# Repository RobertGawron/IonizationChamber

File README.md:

# Ionization Chamber (a device for measuring radioactivity levels)

## Objective

There are many ionization chamber projects online, but most (though not all) produce false positive results. It's cool when a radioactive sample is placed near the detector and the detector shows an increased radiation value, but then, if you place your hand or any non-radioactive object nearby, the readings are high too. This is because, due to high amplification, these devices pick up a lot of noise, making the measurements unreliable.

This project aims to address and eliminate this issue.

## Principle of operation

An ionization chamber is a type of radiation detector that measures ionizing radiation by detecting the charged particles (ions) produced when radiation interacts with the gas inside the chamber. The basic working principle relies on the ionization process. 

* **Radiation Interaction:** When ionizing radiation (such as alpha, beta, or gamma radiation) enters the chamber, it interacts with the gas inside, typically air. This interaction causes the gas molecules to become ionized, producing free electrons and positive ions. 
* **Electric Field:** The chamber contains two electrodes: a central anode and a surrounding cathode. A high voltage is applied between these electrodes, creating an electric field inside the chamber. 
* **Ion Collection:** The free electrons, which are negatively charged, are attracted to the positive anode, while the positively charged ions are attracted to the cathode. As these ions move toward the electrodes, they create an electrical current. 
* **Current Measurement:** The generated current is directly proportional to the number of ions produced, which in turn is related to the amount of radiation that has passed through the chamber. This current is then measured and used to calculate the intensity of the radiation.

Below is an image of the device that was assembled and tested (hardware revision 4.0). Since then, a new version has been developed but has not yet been tested. This repository, in its current state, represents the latest version. For details on the tested version, [refer to 4.0 tag](https://github.com/RobertGawron/IonizationChamber/releases/tag/4.0).  

## System architecture

It is designed in a way that the device can work remotely, e.g. no connection via USB cable to user’s PC is needed.

Remarks:
* The amplifier has three stages (the first stage is a transimpedance amplifier, not a FET transistor like most projects use).
* The ionization chamber is polarized with three 12V batteries connected in series.

## Hardware

PCB was done in KiCAD.

### Hazards

* **The battery container electrodes for chamber polarization are very close to the metal casing; the soldered electrodes should be filed down and secured with insulating tape to prevent short circuits.**
* **The device uses relatively high voltage (32V) to polarize the ionization chamber.** The electrodes of the ionization chamber should not be touched.

## Software

Measurements are collected from the COM port (tunneled over USB) by a Python script and stored in a .csv file. This file can later be parsed using R scripts to generate various diagrams, such as radioactivity changes over time, radioactivity histograms, and box plots for different samples.

* [Details about the firmware are available here.](./Software/Firmware/README.md)
* [Details about the acquisition software are available here.](./Software/MeasurementAcquisition/README.md)
* [Details about the measurement processing software are available here.](./Software/MeasurementAnalysis/README.md)

In the future, data from the device will be gathered and processed using the [HardwareDataLogger project](https://github.com/RobertGawron/HardwareDataLogger), which is currently in development.

## Simulation

A simple mockup was created to generate dummy test data without the need for the real device. This allows testing of the acquisition software (mainly the scripts that generate output diagrams) without requiring hardware.

[More details.](Simulation/README.md)

## DevOps

All software is developed inside a Docker container.

[More information about setting up the environment.](./Documentation/Manuals/README.md)

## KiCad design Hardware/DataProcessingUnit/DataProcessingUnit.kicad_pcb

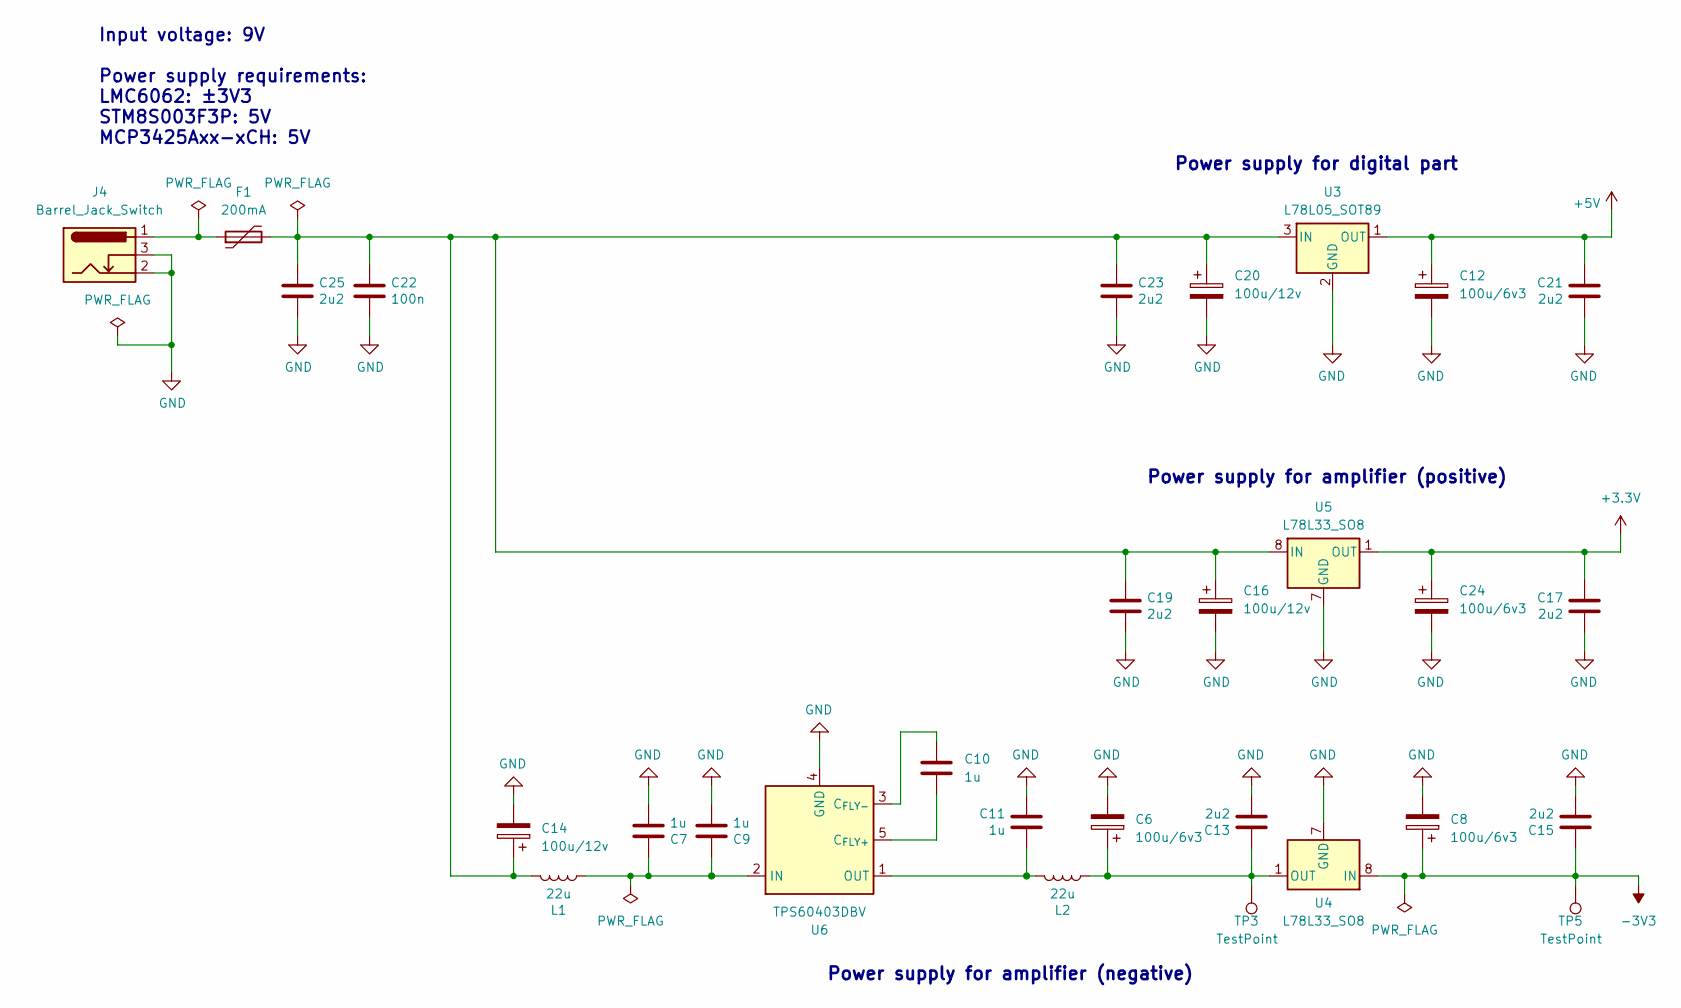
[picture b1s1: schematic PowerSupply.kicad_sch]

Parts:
C6, C8, C24: 100u/6v3; CP_EIA-3528-21_Kemet-B
C7, C9, C10, C11: 1u; C_0805_2012Metric
C12: 100u/6v3; CP_Elec_6.3x5.8
C13, C15, C17, C19, C21, C23, C25: 2u2; C_0805_2012Metric
C14, C16, C20: 100u/12v; CP_Elec_6.3x5.8
C22: 100n; C_0805_2012Metric
F1: 200mA; Fuse_1206_3216Metric
J4: Barrel_Jack_Switch; BarrelJack_GCT_DCJ200-10-A_Horizontal
L1, L2: 22u; L_7.3x7.3_H3.5
TP3, TP5: TestPoint; TestPoint_Pad_D1.0mm
U3: L78L05_SOT89; SOT-89-3
U4, U5: L78L33_SO8; SOIC-8_3.9x4.9mm_P1.27mm
U6: TPS60403DBV; SOT-23-5

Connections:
+3.3V: C17.1, C24.1, U5.1 (OUT); also elsewhere on the board
+5V: C12.1, C21.1, U3.1 (OUT); also elsewhere on the board
-3V3: C8.1, C15.1, TP5.1, U4.8 (IN); also elsewhere on the board
GND: C6.2, C7.2, C8.2, C9.2, C11.2, C12.2, C13.2, C14.2, C15.2, C16.2, C17.2, C19.2, C20.2, C21.2, C22.2, C23.2, C24.2, C25.2, J4.2, J4.3, U3.2 (GND), U4.2 (GND), U4.3 (GND), U4.6 (GND), U4.7 (GND), U5.2 (GND), U5.3 (GND), U5.6 (GND), U5.7 (GND), U6.4 (GND); also elsewhere on the board
unnamed: F1.1, J4.1
unnamed: C14.1, C16.1, C19.1, C20.1, C22.1, C23.1, C25.1, F1.2, L1.2, U3.3 (IN), U5.8 (IN)
unnamed: C6.1, C13.1, L2.1, TP3.1, U4.1 (OUT)
unnamed: C10.2, U6.5 (C_{FLY+})
unnamed: C10.1, U6.3 (C_{FLY-})
unnamed: C7.1, C9.1, L1.1, U6.2 (IN)
unnamed: C11.1, L2.2, U6.1 (OUT)

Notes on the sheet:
Power supply for amplifier (negative)
Power supply for amplifier (positive)
Power supply for digital part
Input voltage: 9V Power supply requirements: LMC6062: ±3V3 STM8S003F3P: 5V MCP3425Axx-xCH: 5V

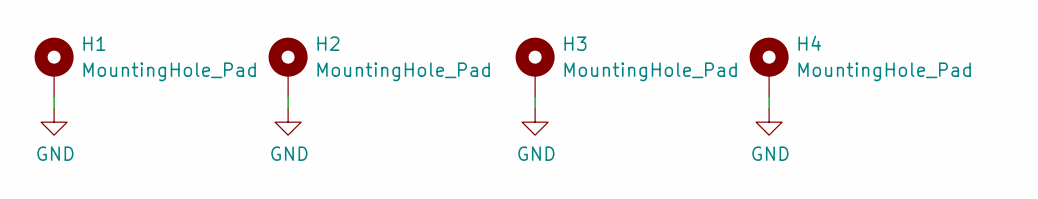
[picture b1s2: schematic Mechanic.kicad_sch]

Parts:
H1, H2, H3, H4: MountingHole_Pad; MountingHole_3.5mm_Pad

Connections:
GND: H1.1, H2.1, H3.1, H4.1; also elsewhere on the board

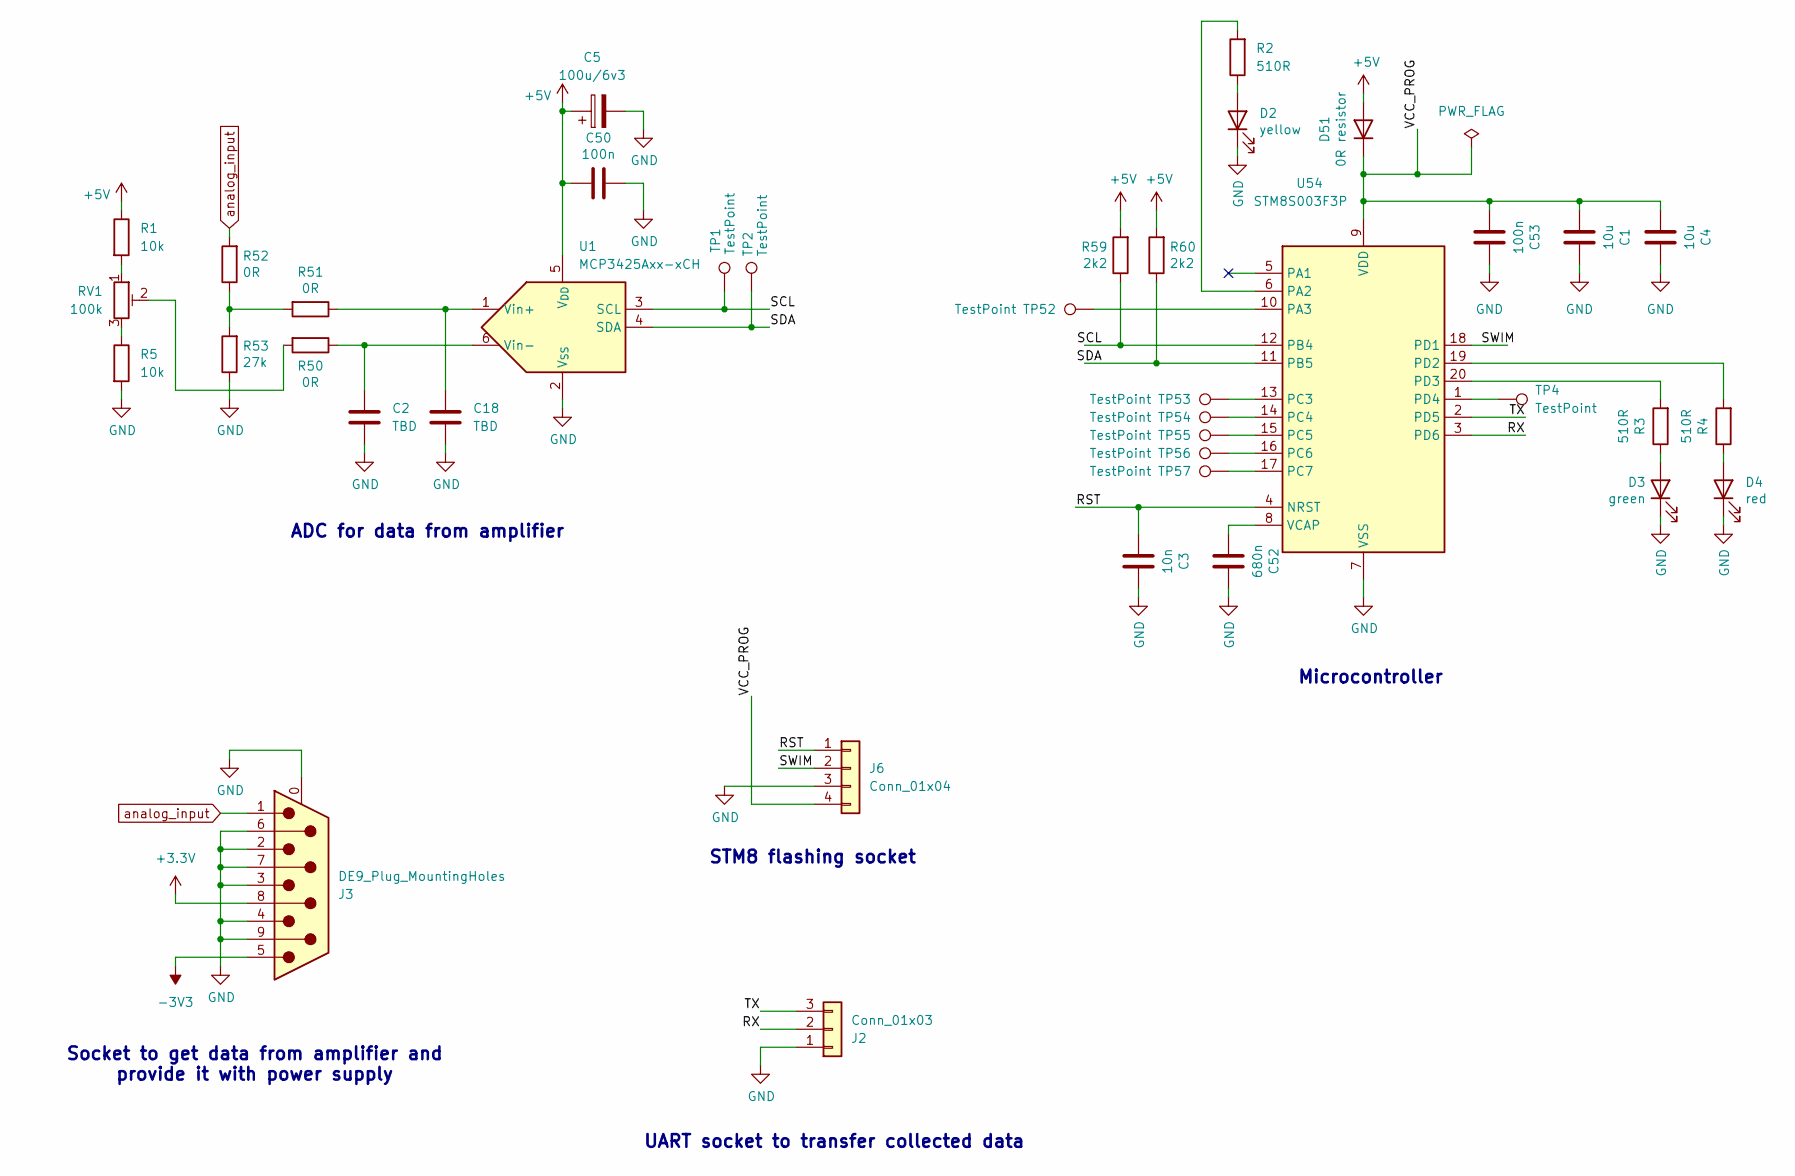
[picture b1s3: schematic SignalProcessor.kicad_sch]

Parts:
C1, C4: 10u; C_0805_2012Metric
C2, C18: TBD; C_0805_2012Metric
C3: 10n; C_0805_2012Metric
C5: 100u/6v3; CP_EIA-3528-21_Kemet-B
C50, C53: 100n; C_0805_2012Metric
C52: 680n; C_0805_2012Metric
D2: yellow; LED_0805_2012Metric
D3: green; LED_0805_2012Metric
D4: red; LED_0805_2012Metric
D51: 0R resistor; D_MiniMELF
J2: Conn_01x03; PinSocket_1x03_P2.54mm_Horizontal
J3: DE9_Plug_MountingHoles; DSUB-9_Male_Vertical_P2.77x2.84mm_MountingHoles
J6: Conn_01x04; PinSocket_1x04_P2.54mm_Horizontal
R1, R5: 10k; R_0805_2012Metric
R2, R3, R4: 510R; R_0805_2012Metric
R50, R51, R52: 0R; R_0805_2012Metric
R53: 27k; R_0805_2012Metric
R59, R60: 2k2; R_0805_2012Metric
RV1: 100k; Potentiometer_Bourns_3296W_Vertical
TP1, TP2, TP4, TP52, TP53, TP54, TP55, TP56, TP57: TestPoint; TestPoint_Pad_D1.0mm
U1: MCP3425Axx-xCH; SOT-23-6
U54: STM8S003F3P; TSSOP-20_4.4x6.5mm_P0.65mm

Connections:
+3.3V: J3.8; also elsewhere on the board
+5V: C5.1, C50.2, D51.2 (A), R1.1, R59.2, R60.2, U1.5 (V_{DD}); also elsewhere on the board
-3V3: J3.5; also elsewhere on the board
/SignalProcessor/RST: C3.2, J6.1, U54.4 (NRST)
/SignalProcessor/RX: J2.2, U54.3 (PD6)
/SignalProcessor/SCL: R59.1, TP1.1, U1.3 (SCL), U54.12 (PB4)
/SignalProcessor/SDA: R60.1, TP2.1, U1.4 (SDA), U54.11 (PB5)
/SignalProcessor/SWIM: J6.2, U54.18 (PD1)
/SignalProcessor/TX: J2.3, U54.2 (PD5)
/SignalProcessor/VCC_PROG: C1.2, C4.2, C53.2, D51.1 (K), J6.4, U54.9 (VDD)
GND: C1.1, C2.2, C3.1, C4.1, C5.2, C18.2, C50.1, C52.1, C53.1, D2.1 (K), D3.1 (K), D4.1 (K), J2.1, J3.0 (PAD), J3.2, J3.3, J3.4, J3.6, J3.7, J3.9, J6.3, R5.2, R53.1, U1.2 (V_{SS}), U54.7 (VSS); also elsewhere on the board
unnamed: D2.2 (A), R2.1
unnamed: D3.2 (A), R3.1
unnamed: D4.2 (A), R4.1
unnamed: R1.2, RV1.1
unnamed: R5.1, RV1.3
unnamed: R50.2, RV1.2
unnamed: R51.2, R52.1, R53.2
unnamed: C18.1, R51.1, U1.1 (Vin+)
unnamed: C2.1, R50.1, U1.6 (Vin-)
unnamed: R2.2, U54.6 (PA2)
unnamed: TP52.1, U54.10 (PA3)
unnamed: TP53.1, U54.13 (PC3)
unnamed: TP54.1, U54.14 (PC4)
unnamed: TP55.1, U54.15 (PC5)
unnamed: TP56.1, U54.16 (PC6)
unnamed: TP57.1, U54.17 (PC7)
unnamed: R4.2, U54.19 (PD2)
unnamed: R3.2, U54.20 (PD3)
unnamed: TP4.1, U54.1 (PD4)
unnamed: C52.2, U54.8 (VCAP)
analog_input: J3.1, R52.2

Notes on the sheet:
Socket to get data from amplifier and provide it with power supply
Microcontroller
ADC for data from amplifier
STM8 flashing socket
UART socket to transfer collected data

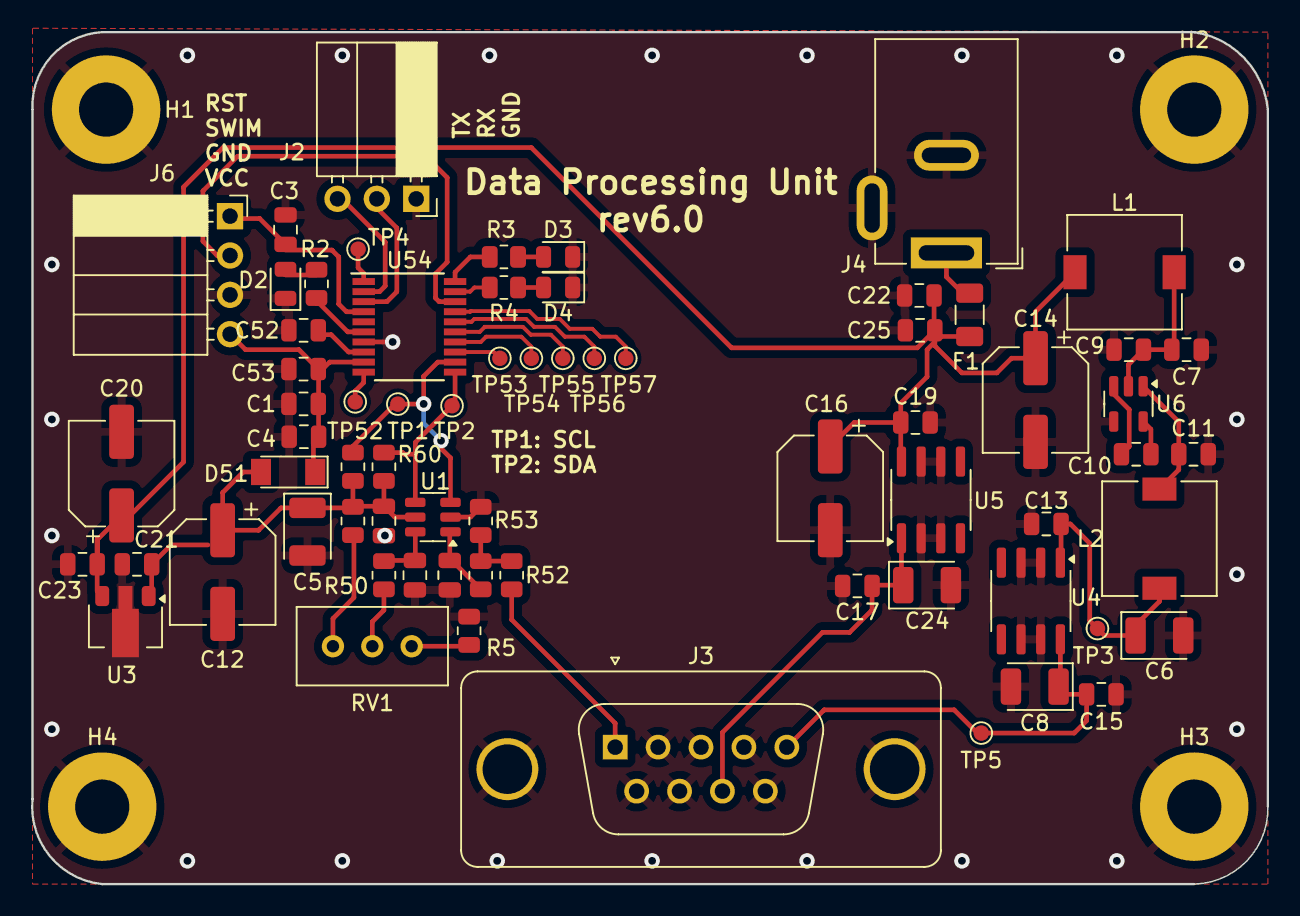
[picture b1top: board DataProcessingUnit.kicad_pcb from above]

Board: 2 copper layers, 79.8 x 55.0 mm, 72 parts (0 on the bottom side), 39 nets.

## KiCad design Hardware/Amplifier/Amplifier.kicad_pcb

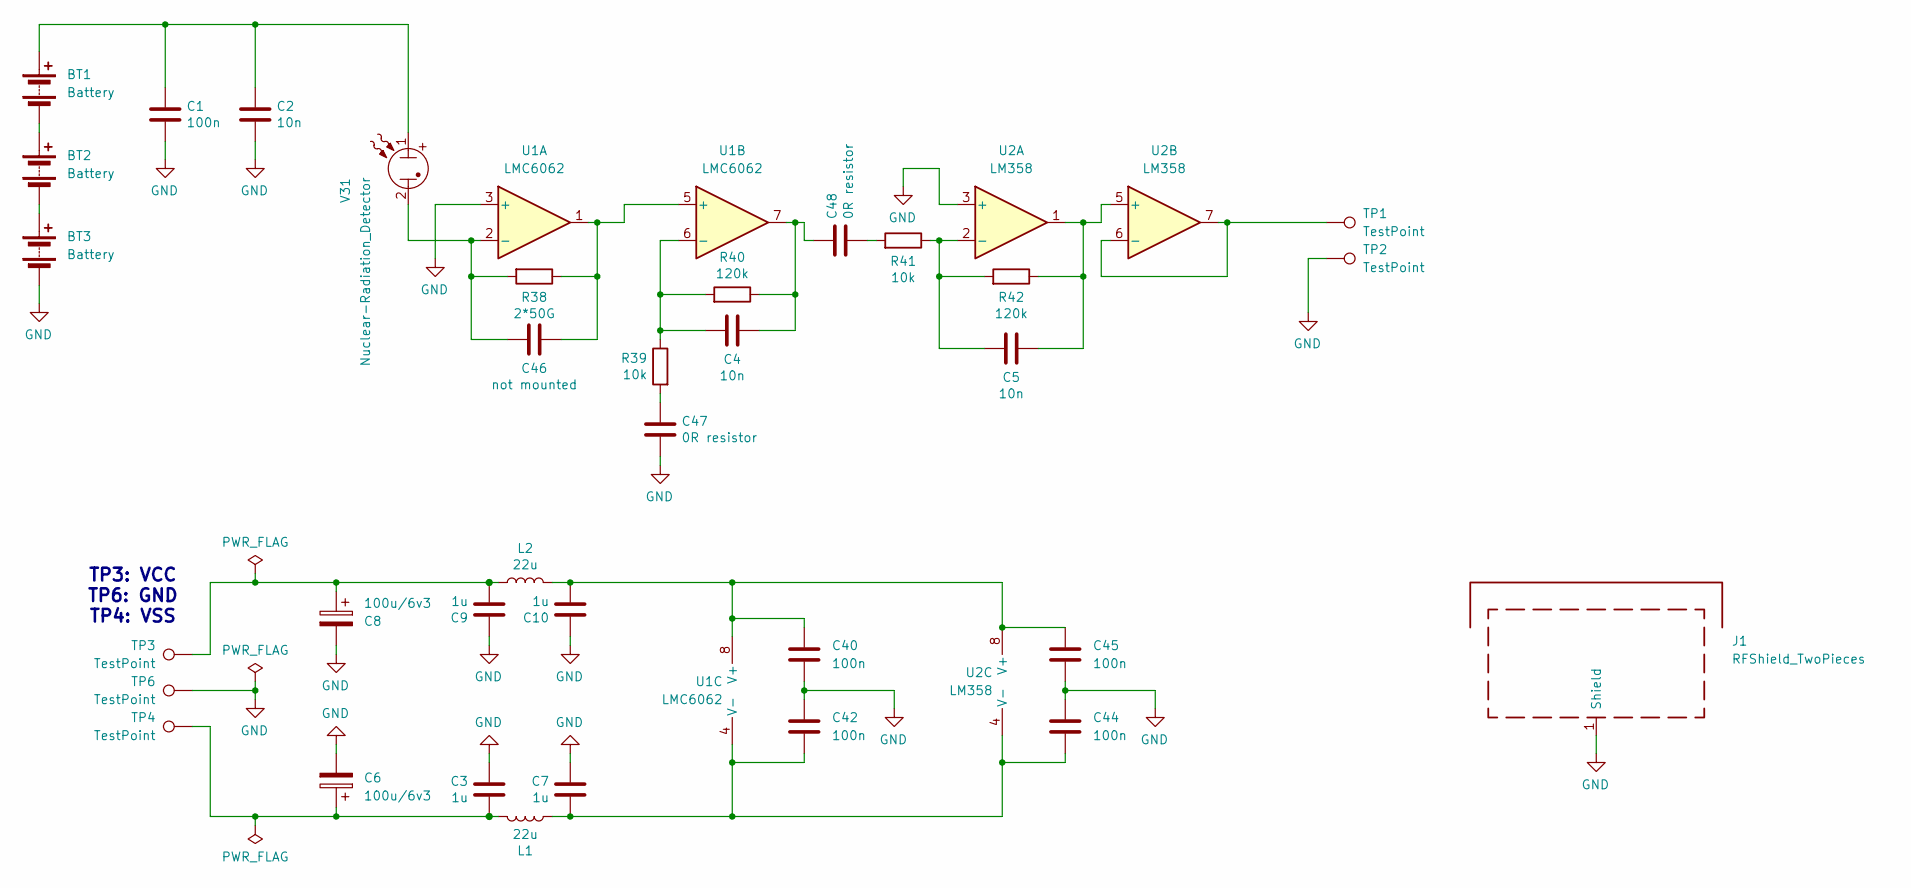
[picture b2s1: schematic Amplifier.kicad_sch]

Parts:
BT1, BT2, BT3: Battery; AAAAPCBHolder
C1, C40, C42, C44, C45: 100n; C_0805_2012Metric
C2, C4, C5: 10n; C_0805_2012Metric
C3, C7, C9, C10: 1u; C_0805_2012Metric
C6, C8: 100u/6v3; CP_EIA-3528-21_Kemet-B
C46: not mounted; C_0805_2012Metric
C47, C48: 0R resistor; C_0805_2012Metric
J1: RFShield_TwoPieces; IonizationChamberShield
L1, L2: 22u; L_7.3x7.3_H3.5
R38: 2*50G; R_0805_2012Metric_Pad1.15x1.40mm_HandSolder
R39, R41: 10k; R_0805_2012Metric
R40, R42: 120k; R_0805_2012Metric
TP1, TP2, TP3, TP4, TP6: TestPoint; TestPoint_Loop_D2.60mm_Drill0.9mm_Beaded
U1: LMC6062; DIP-8_W7.62mm
U2: LM358; SO-8_3.9x4.9mm_P1.27mm
V31: Nuclear-Radiation_Detector; IonizationChamberSensor

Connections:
GND: BT3.2 (-), C1.2, C2.2, C3.2, C6.2, C7.2, C8.2, C9.2, C10.2, C40.2, C42.2, C44.2, C45.1, C47.2, J1.1 (Shield), TP2.1, TP6.1, U1.3 (+), U2.3 (+)
unnamed: BT1.1 (+), C1.1, C2.1, V31.1
unnamed: BT1.2 (-), BT2.1 (+)
unnamed: BT2.2 (-), BT3.1 (+)
unnamed: C3.1, C6.1, L1.2, TP4.1
unnamed: C4.2, C48.1, R40.1, U1.7
unnamed: C8.1, C9.1, L2.2, TP3.1
unnamed: C47.1, R39.2
unnamed: C48.2, R41.2
unnamed: C46.2, R38.2, U1.2 (-), V31.2
unnamed: C46.1, R38.1, U1.1, U1.5 (+)
unnamed: C4.1, R39.1, R40.2, U1.6 (-)
unnamed: C10.1, C40.1, C45.2, L2.1, U1.8 (V+), U2.8 (V+)
unnamed: C7.1, C42.1, C44.1, L1.1, U1.4 (V-), U2.4 (V-)
unnamed: C5.1, R41.1, R42.2, U2.2 (-)
unnamed: C5.2, R42.1, U2.1, U2.5 (+)
unnamed: TP1.1, U2.6 (-), U2.7

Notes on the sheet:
TP3: VCC TP6: GND TP4: VSS

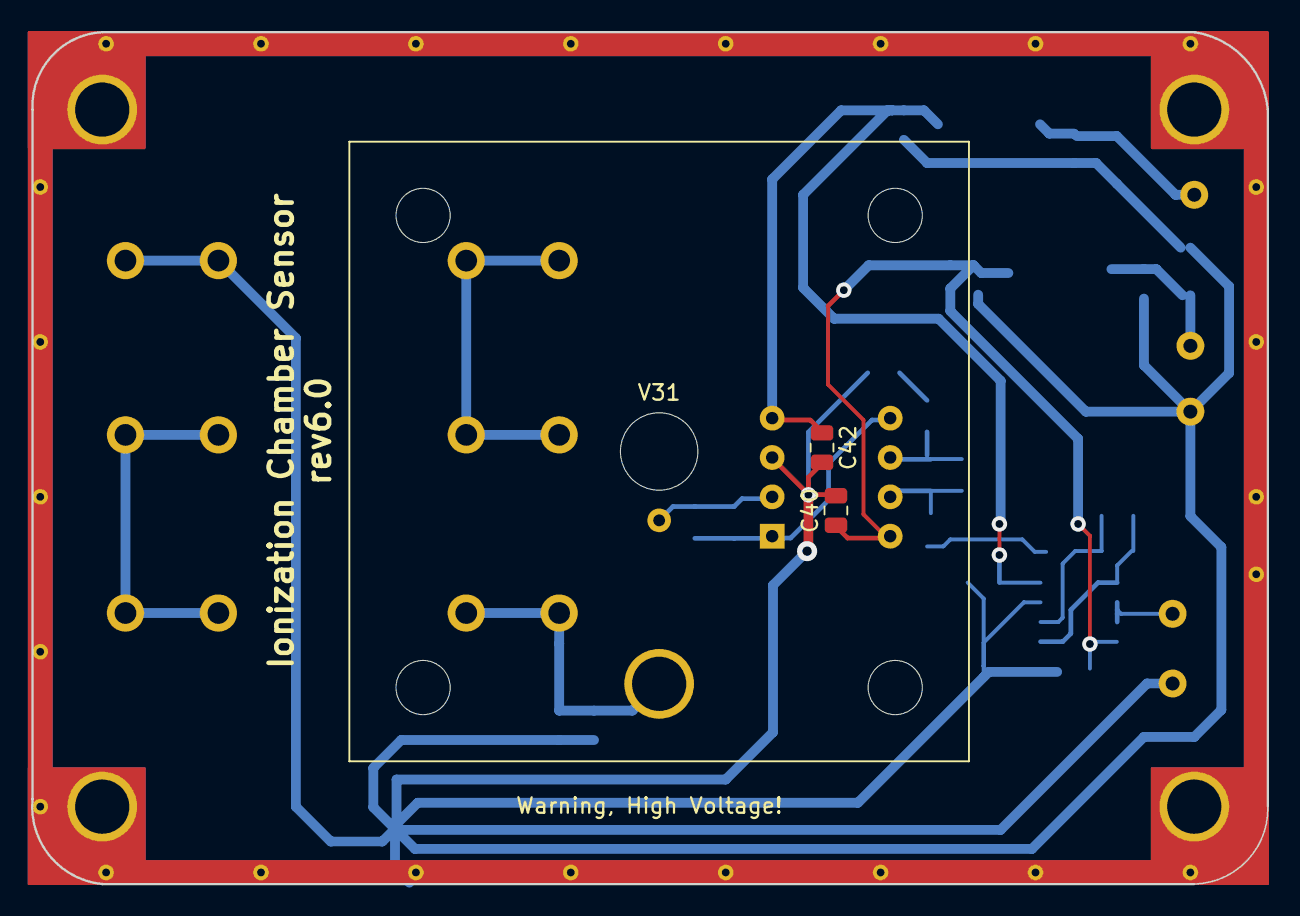
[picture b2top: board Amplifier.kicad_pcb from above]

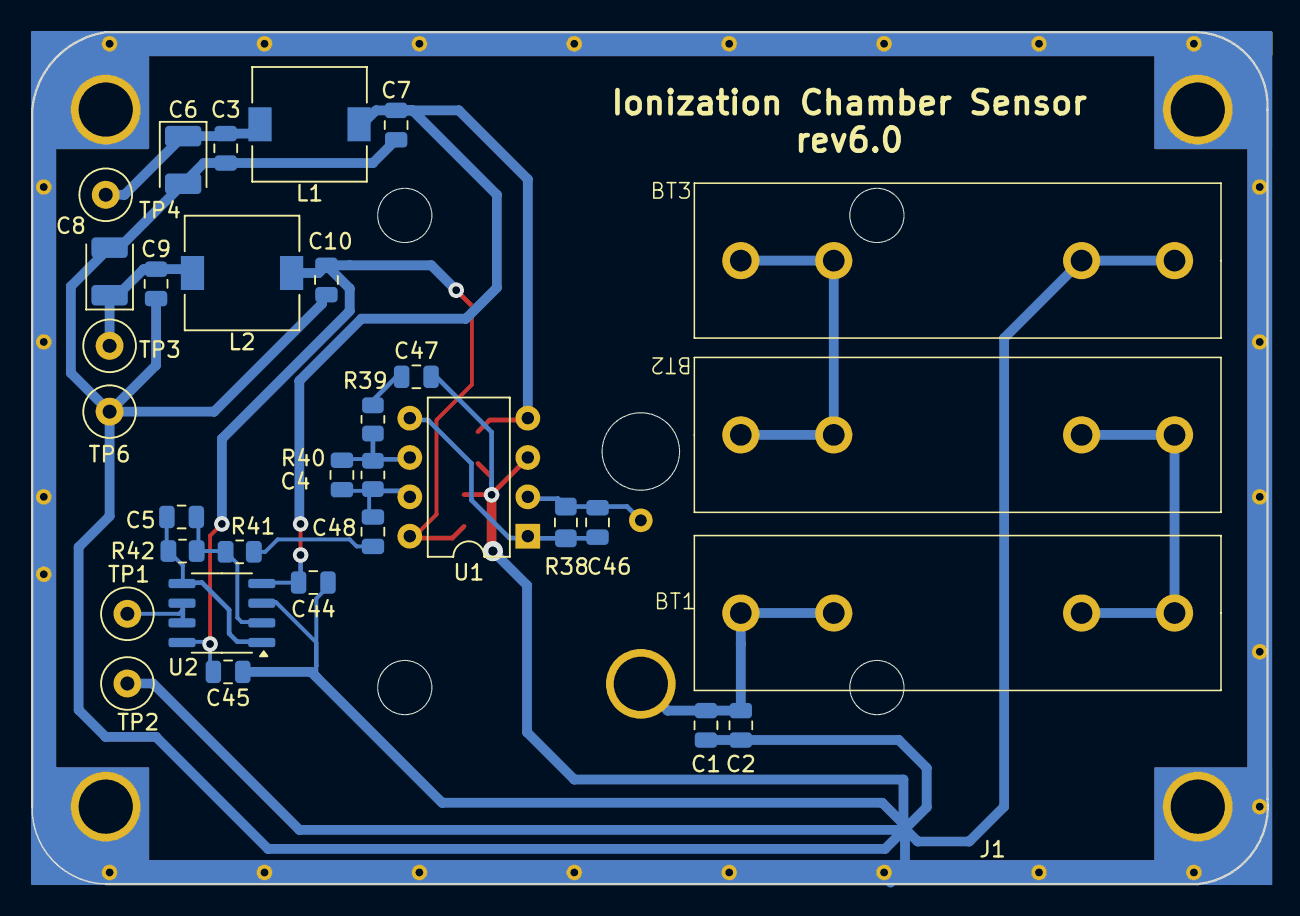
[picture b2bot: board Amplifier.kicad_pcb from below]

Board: 2 copper layers, 79.8 x 55.0 mm, 36 parts (33 on the bottom side), 17 nets.

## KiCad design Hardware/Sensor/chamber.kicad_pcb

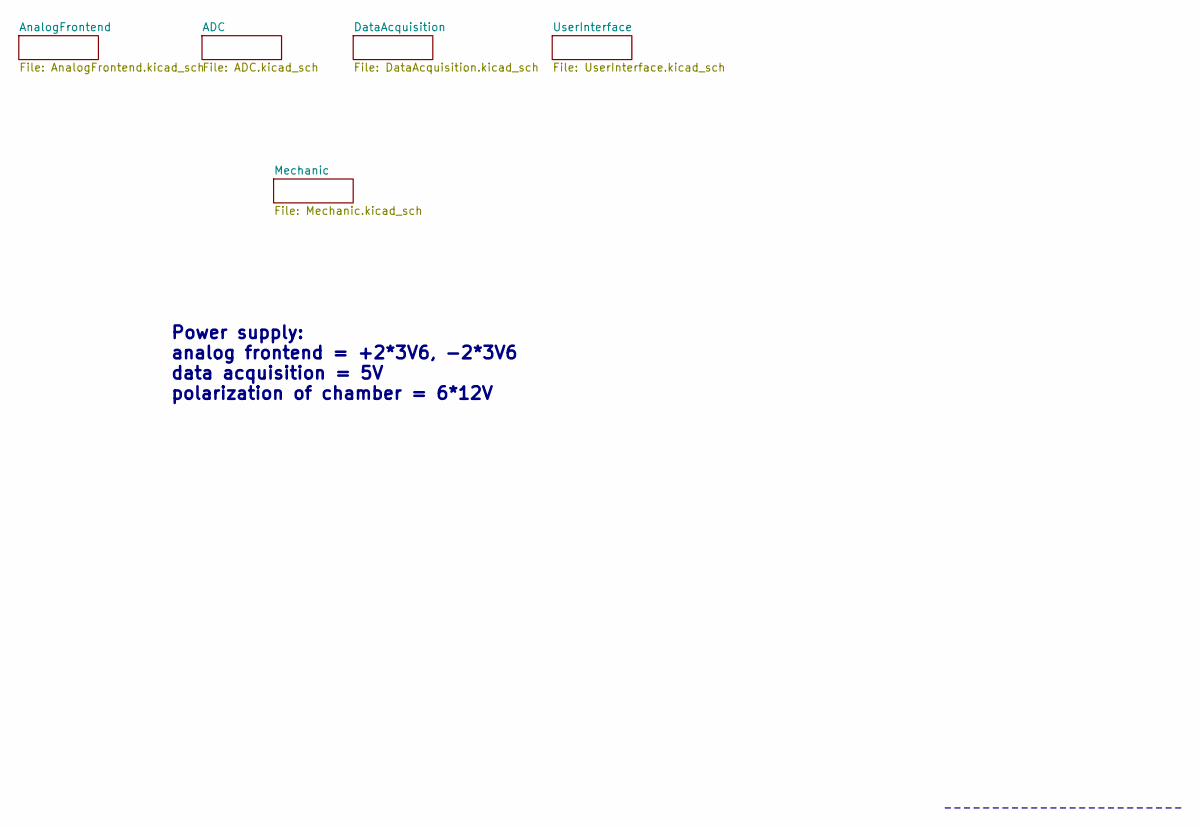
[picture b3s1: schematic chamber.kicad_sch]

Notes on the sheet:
Power supply: analog frontend = +2*3V6, -2*3V6 data acquisition = 5V polarization of chamber = 6*12V

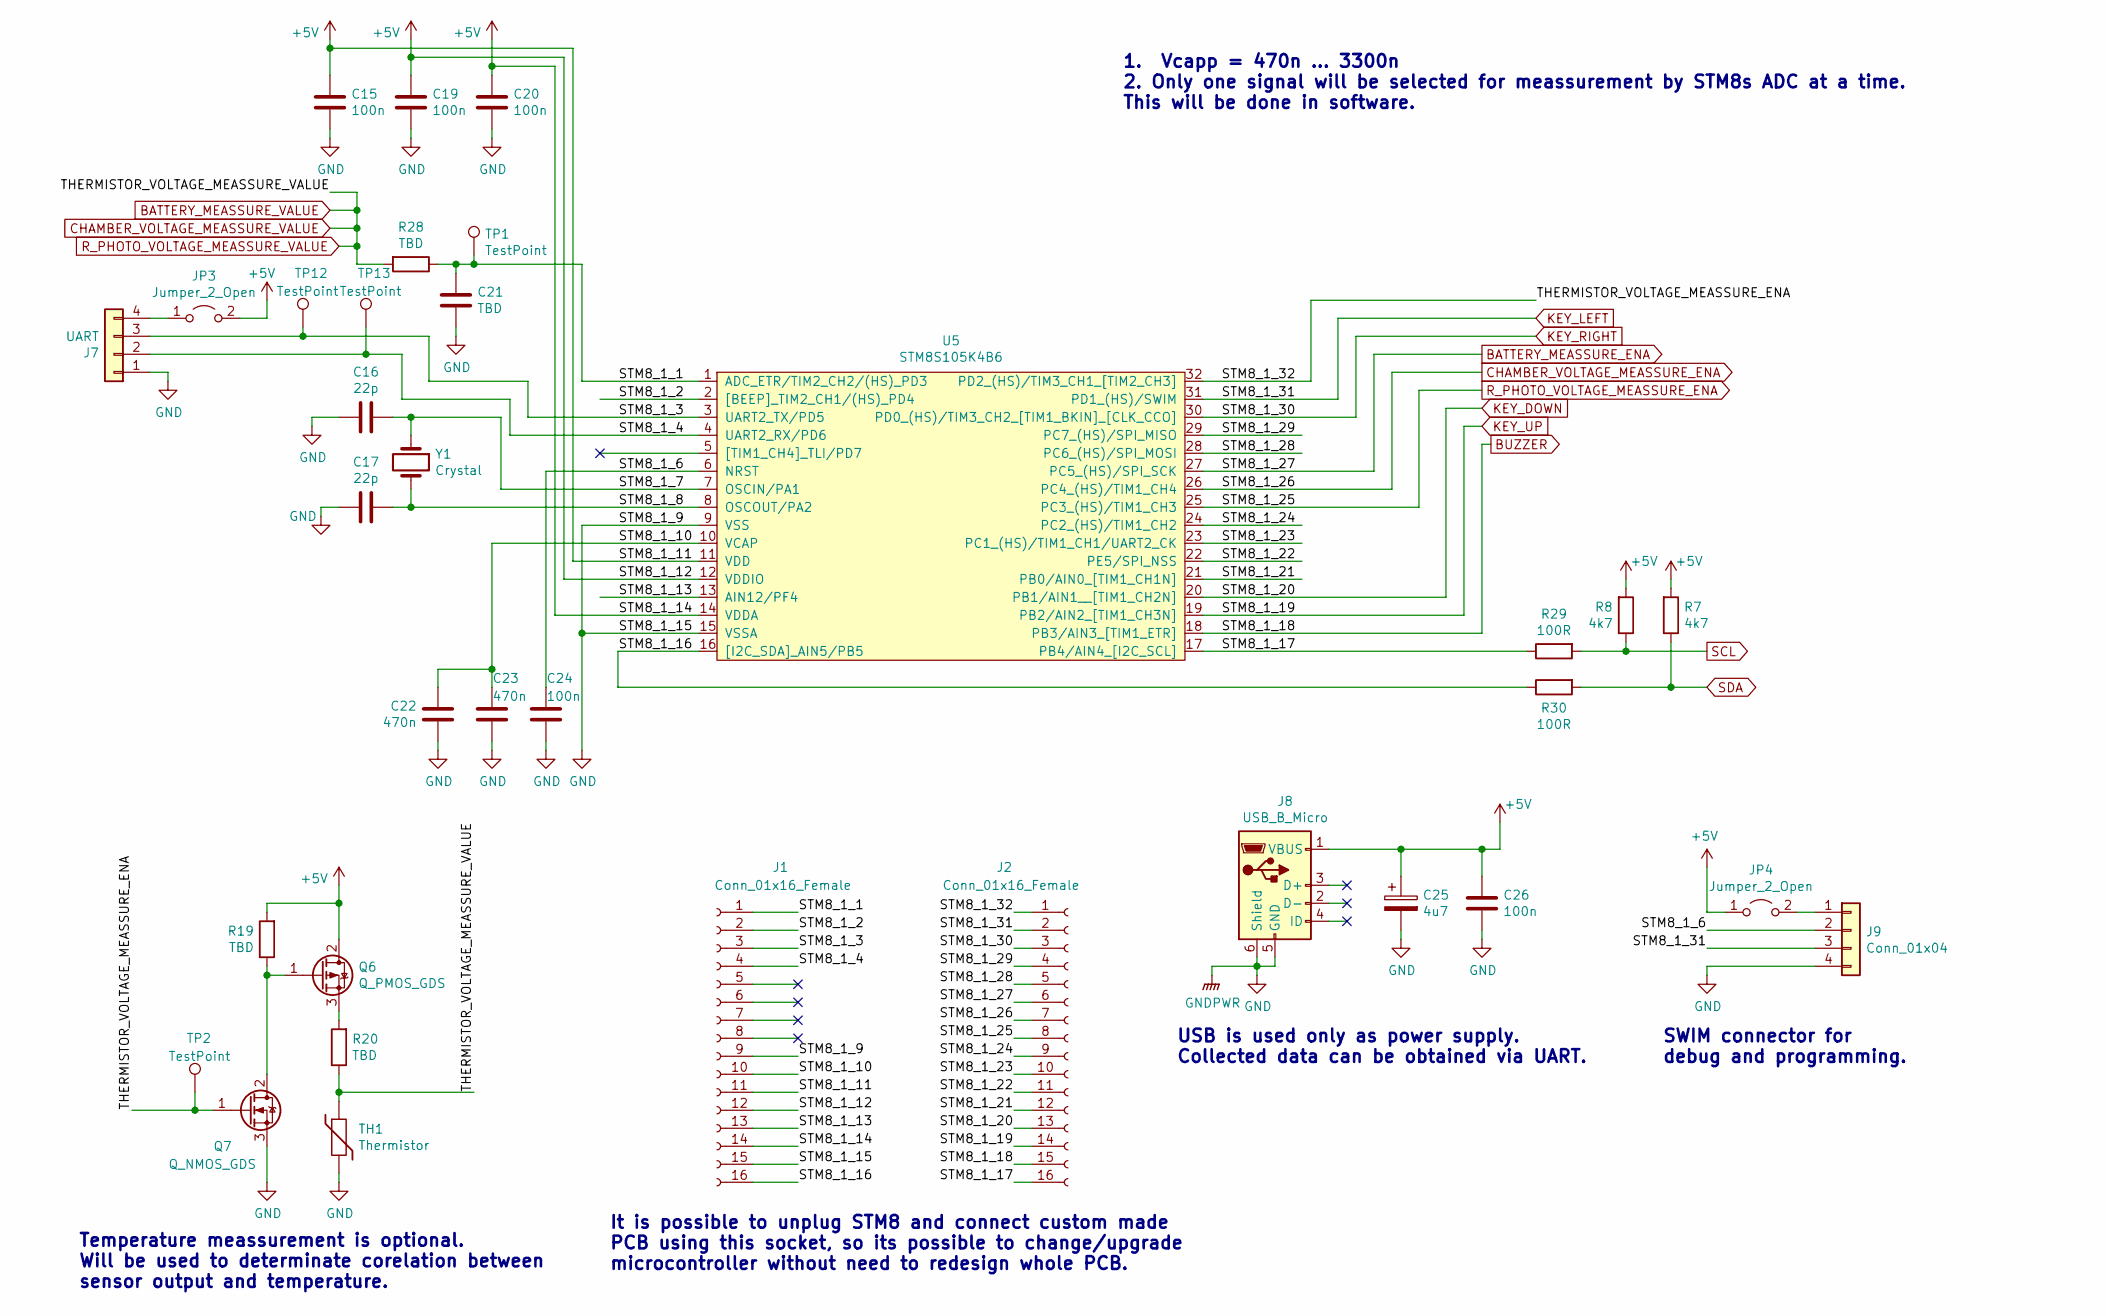
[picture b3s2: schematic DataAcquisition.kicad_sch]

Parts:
C15, C19, C20, C24, C26: 100n; C_0805_2012Metric; LCSC C282732
C16, C17: 22p; C_0805_2012Metric
C21: TBD; C_0805_2012Metric
C22, C23: 470n; C_0805_2012Metric
C25: 4u7; CP_EIA-3528-21_Kemet-B
J1, J2: Conn_01x16_Female; PinSocket_1x16_P2.54mm_Vertical
J7: UART; PinSocket_1x04_P2.54mm_Horizontal
J8: USB_B_Micro; USB_Micro-B_Molex-105017-0001
J9: Conn_01x04; PinSocket_1x04_P2.54mm_Vertical
JP3, JP4: Jumper_2_Open; SolderJumper-2_P1.3mm_Open_Pad1.0x1.5mm
Q6: Q_PMOS_GDS; SOT-23
Q7: Q_NMOS_GDS; SOT-23
R7, R8: 4k7; R_0805_2012Metric; LCSC C25900
R19, R20, R28: TBD; R_0805_2012Metric
R29, R30: 100R; R_0805_2012Metric; LCSC C17408
TH1: Thermistor; R_0805_2012Metric
TP1, TP2, TP12, TP13: TestPoint; TestPoint_Pad_D2.0mm
U5: STM8S105K4B6; DIP-32_400_ELL
Y1: Crystal; Crystal_SMD_5032-2Pin_5.0x3.2mm_HandSoldering

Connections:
+5V: C15.1, C19.1, C20.1, C25.1, C26.1, J1.11, J1.12, J1.14, J8.1 (VBUS), JP3.2 (B), JP4.1 (A), Q6.2 (D), R7.2, R8.2, R19.2, U5.11 (VDD), U5.12 (VDDIO), U5.14 (VDDA); also elsewhere on the board
/DataAcquisition/STM8_1_1: C21.1, J1.1, R28.1, TP1.1, U5.1 (ADC_ETR/TIM2_CH2/(HS)_PD3)
/DataAcquisition/STM8_1_2: J1.2, U5.2 ([BEEP]_TIM2_CH1/(HS)_PD4)
/DataAcquisition/STM8_1_3: J1.3, J7.3, TP12.1, U5.3 (UART2_TX/PD5)
/DataAcquisition/STM8_1_4: J1.4, J7.2, TP13.1, U5.4 (UART2_RX/PD6)
/DataAcquisition/STM8_1_6: C24.1, J9.2, U5.6 (NRST)
/DataAcquisition/STM8_1_7: C16.1, U5.7 (OSCIN/PA1), Y1.1
/DataAcquisition/STM8_1_8: C17.1, U5.8 (OSCOUT/PA2), Y1.2
/DataAcquisition/STM8_1_10: C22.1, C23.1, J1.10, U5.10 (VCAP)
/DataAcquisition/STM8_1_13: J1.13, U5.13 (AIN12/PF4)
/DataAcquisition/STM8_1_16: J1.16, R30.1, U5.16 ([I2C_SDA]_AIN5/PB5)
/DataAcquisition/STM8_1_17: J2.16, R29.1, U5.17 (PB4/AIN4_[I2C_SCL])
/DataAcquisition/STM8_1_21: J2.12, U5.21 (PB0/AIN0_[TIM1_CH1N])
/DataAcquisition/STM8_1_22: J2.11, U5.22 (PE5/SPI_NSS)
/DataAcquisition/STM8_1_23: J2.10, U5.23 (PC1_(HS)/TIM1_CH1/UART2_CK)
/DataAcquisition/STM8_1_24: J2.9, U5.24 (PC2_(HS)/TIM1_CH2)
/DataAcquisition/STM8_1_28: J2.5, U5.28 (PC6_(HS)/SPI_MOSI)
/DataAcquisition/STM8_1_29: J2.4, U5.29 (PC7_(HS)/SPI_MISO)
/DataAcquisition/STM8_1_32: J2.1, Q7.1 (G), TP2.1, U5.32 (PD2_(HS)/TIM3_CH1_[TIM2_CH3])
BATTERY_MEASSURE_ENA: J2.6, U5.27 (PC5_(HS)/SPI_SCK); also elsewhere on the board
BATTERY_MEASSURE_VALUE: R20.1, R28.2, TH1.1; also elsewhere on the board
BUZZER: J2.15, U5.18 (PB3/AIN3_[TIM1_ETR]); also elsewhere on the board
CHAMBER_VOLTAGE_MEASSURE_ENA: J2.7, U5.26 (PC4_(HS)/TIM1_CH4); also elsewhere on the board
GND: C15.2, C16.2, C17.2, C19.2, C20.2, C21.2, C22.2, C23.2, C24.2, C25.2, C26.2, J1.9, J1.15, J7.1, J8.5 (GND), J8.6 (Shield), J9.4, Q7.3 (S), TH1.2, U5.9 (VSS), U5.15 (VSSA); also elsewhere on the board
KEY_DOWN: J2.13, U5.20 (PB1/AIN1__[TIM1_CH2N]); also elsewhere on the board
KEY_LEFT: J2.2, J9.3, U5.31 (PD1_(HS)/SWIM); also elsewhere on the board
KEY_RIGHT: J2.3, U5.30 (PD0_(HS)/TIM3_CH2_[TIM1_BKIN]_[CLK_CCO]); also elsewhere on the board
KEY_UP: J2.14, U5.19 (PB2/AIN2_[TIM1_CH3N]); also elsewhere on the board
unnamed: J7.4, JP3.1 (A)
unnamed: J9.1, JP4.2 (B)
unnamed: Q6.1 (G), Q7.2 (D), R19.1
unnamed: Q6.3 (S), R20.2
R_PHOTO_VOLTAGE_MEASSURE_ENA: J2.8, U5.25 (PC3_(HS)/TIM1_CH3); also elsewhere on the board
SCL: R8.1, R29.2; also elsewhere on the board
SDA: R7.1, R30.2; also elsewhere on the board

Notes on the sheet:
Temperature meassurement is optional. Will be used to determinate corelation between sensor output and temperature.
It is possible to unplug STM8 and connect custom made PCB using this socket, so its possible to change/upgrade microcontroller without need to redesign whole PCB.
1. Vcapp = 470n ... 3300n 2. Only one signal will be selected for meassurement by STM8s ADC at a time. This will be done in software.
USB is used only as power supply. Collected data can be obtained via UART.
SWIM connector for debug and programming.
